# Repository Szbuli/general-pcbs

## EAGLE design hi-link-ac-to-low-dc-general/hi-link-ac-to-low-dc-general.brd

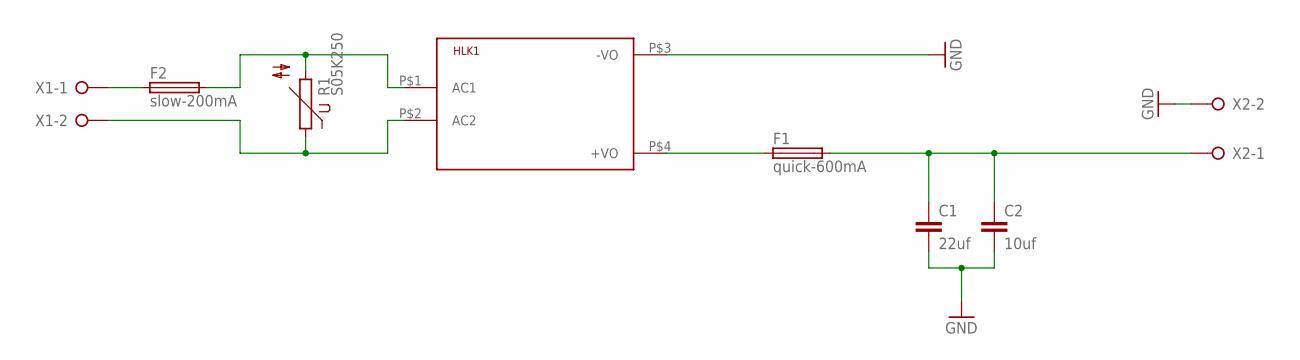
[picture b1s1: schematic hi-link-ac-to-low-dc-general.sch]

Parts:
C1: 22uf; C1206
C2: 10uf; C1206
F1: quick-600mA; SH22,5
F2: slow-200mA; SH22,5
HLK1: HLK-PM013W; HLK-PM01
R1: S05K250
X1, X2: W237-02P; W237-132

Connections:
GND: C1.2, C2.2, HLK1.P$3 (-VO), X2.2
unnamed: F2.1, X1.1
unnamed: F2.2, HLK1.P$1 (AC1), R1.2
unnamed: C1.1, C2.1, F1.2, X2.1
unnamed: F1.1, HLK1.P$4 (+VO)
unnamed: HLK1.P$2 (AC2), R1.1, X1.2

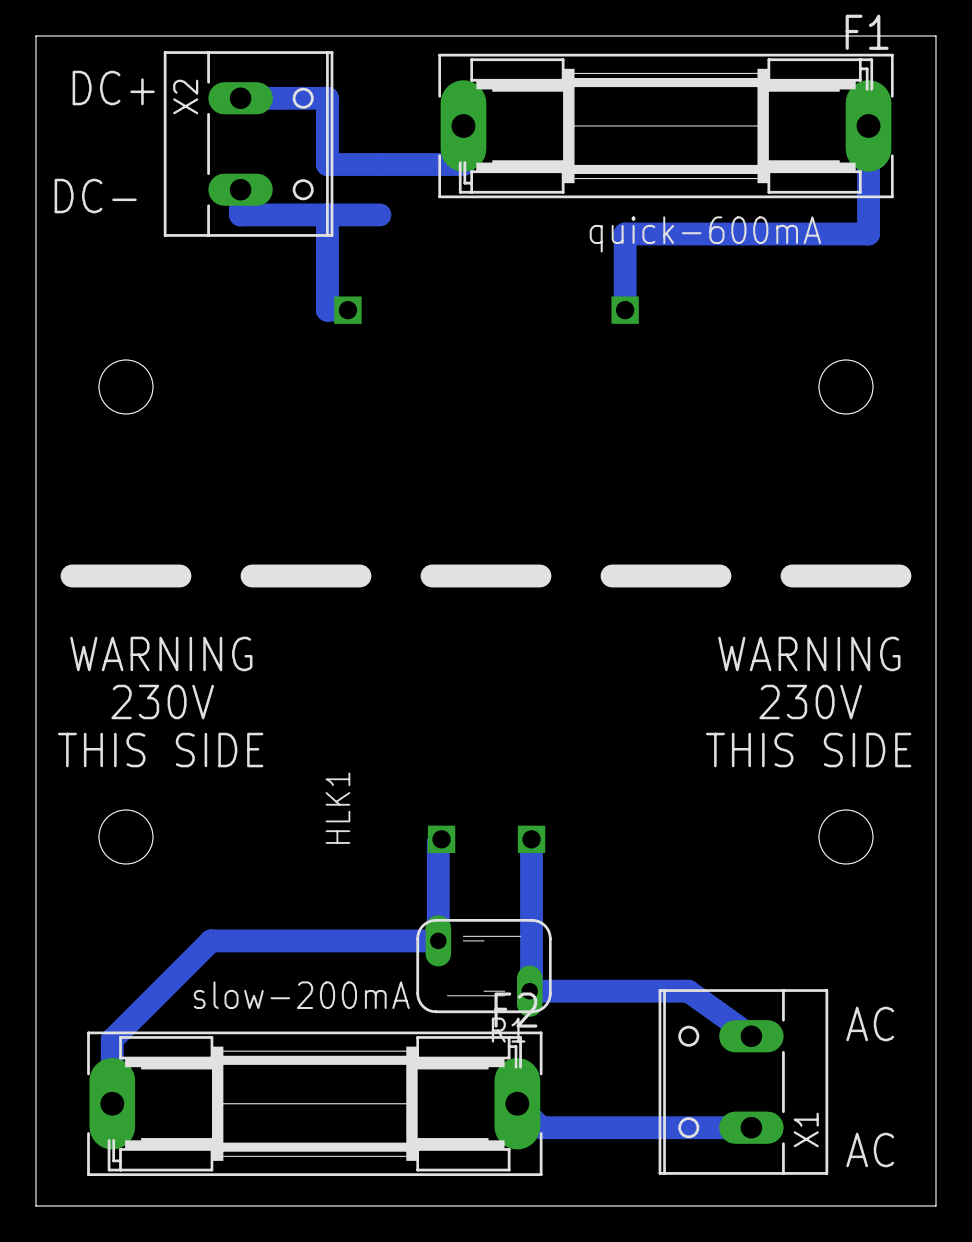
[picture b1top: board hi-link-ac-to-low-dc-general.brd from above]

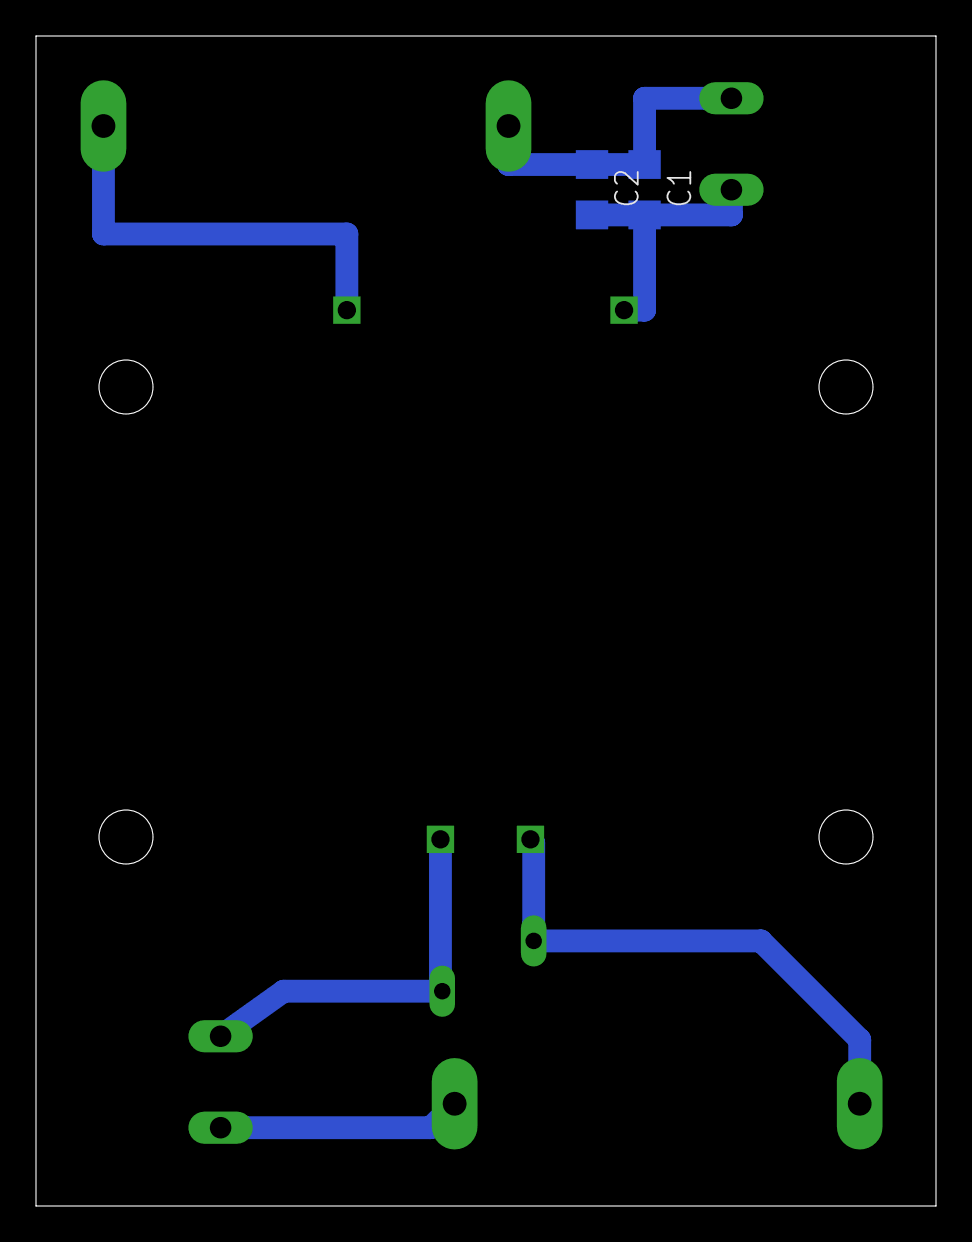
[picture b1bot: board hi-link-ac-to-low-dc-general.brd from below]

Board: 2 copper layers, 50.0 x 65.0 mm, 10 parts (2 on the bottom side), 6 nets.

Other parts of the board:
U$1, U$2: DIN-MOUNT-2-HOLE

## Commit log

2020-04-16 hi-link-ac-to-low-dc-general
2020-04-16 hi-link-ac-to-low-dc-general update text layer to silk
2020-05-08 add logo
